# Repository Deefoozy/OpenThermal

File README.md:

# OpenThermal
Thermal camera project

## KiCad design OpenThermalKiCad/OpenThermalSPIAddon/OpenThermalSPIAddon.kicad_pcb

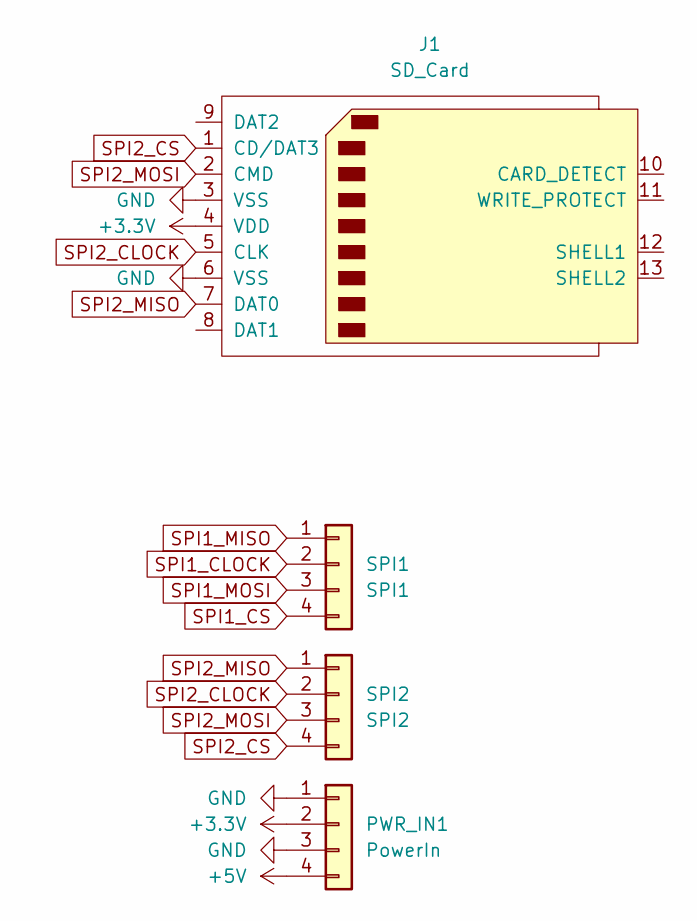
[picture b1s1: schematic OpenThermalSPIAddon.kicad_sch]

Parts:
J1: SD_Card; SD_Kyocera_145638009211859+
PWR_IN1: PowerIn; PinSocket_1x04_P2.54mm_Vertical
SPI1: SPI1; PinSocket_1x04_P2.54mm_Vertical
SPI2: SPI2; PinSocket_1x04_P2.54mm_Vertical

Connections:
+3.3V: J1.4 (VDD), PWR_IN1.2
+5V: PWR_IN1.4
GND: J1.3 (VSS), J1.6 (VSS), PWR_IN1.1, PWR_IN1.3
SPI1_CLOCK: SPI1.2
SPI1_CS: SPI1.4
SPI1_MISO: SPI1.1
SPI1_MOSI: SPI1.3
SPI2_CLOCK: J1.5 (CLK), SPI2.2
SPI2_CS: J1.1 (CD/DAT3), SPI2.4
SPI2_MISO: J1.7 (DAT0), SPI2.1
SPI2_MOSI: J1.2 (CMD), SPI2.3

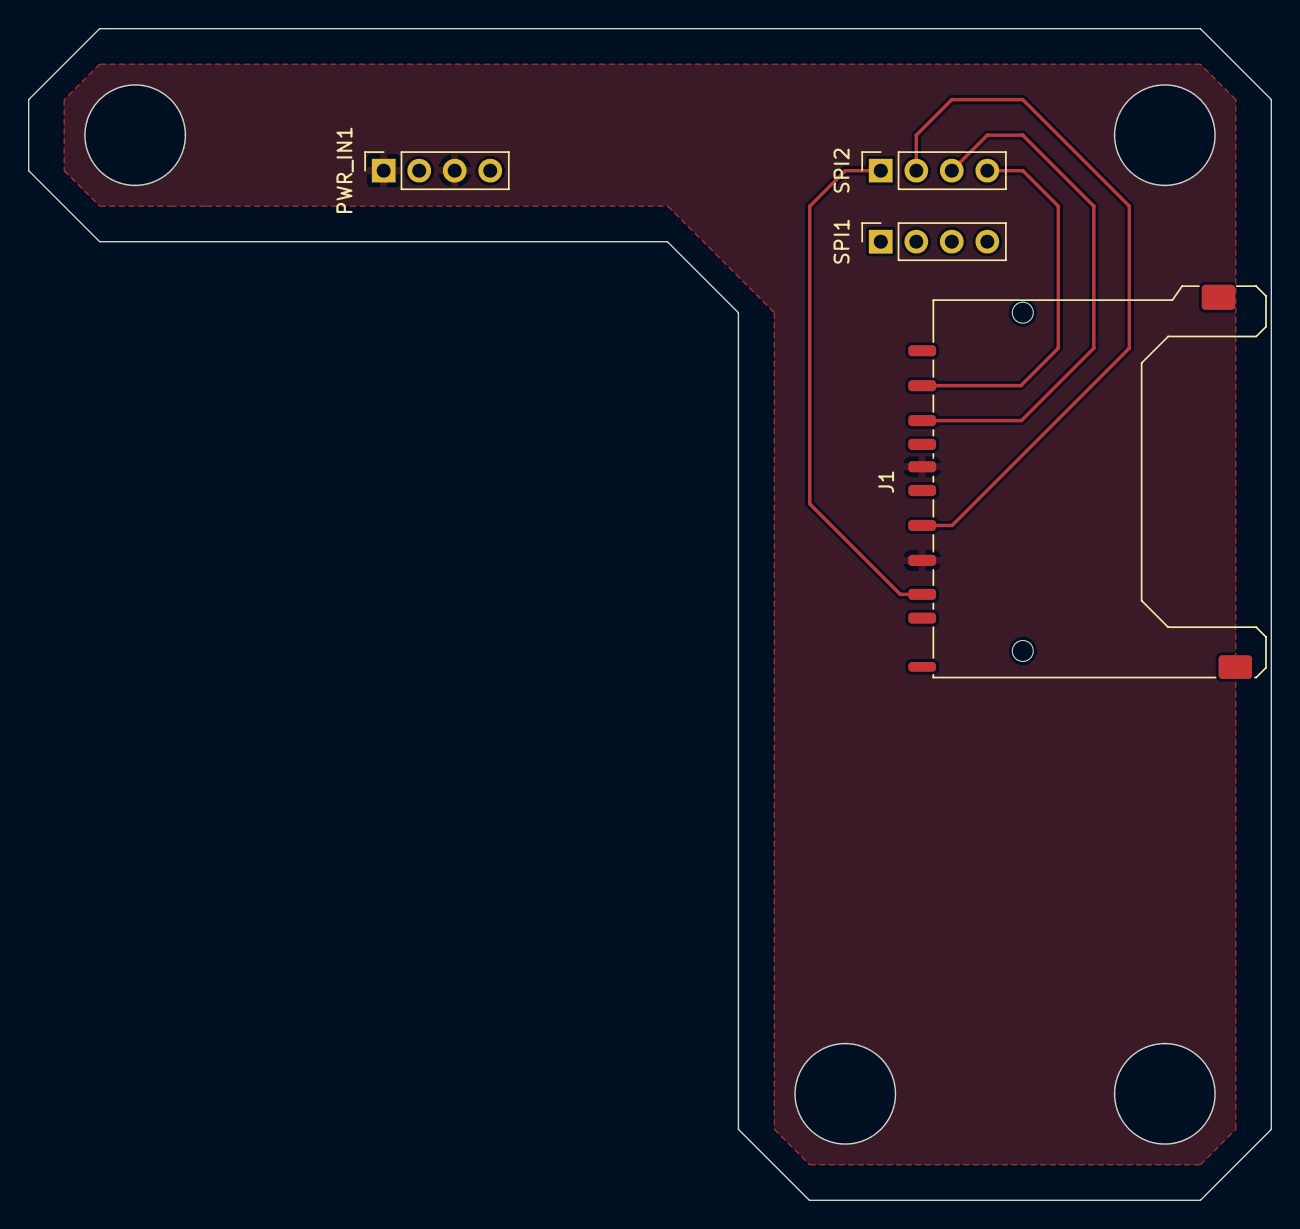
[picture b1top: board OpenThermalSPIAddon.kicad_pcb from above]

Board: 2 copper layers, 88.9 x 83.8 mm, 4 parts (0 on the bottom side), 6 nets.

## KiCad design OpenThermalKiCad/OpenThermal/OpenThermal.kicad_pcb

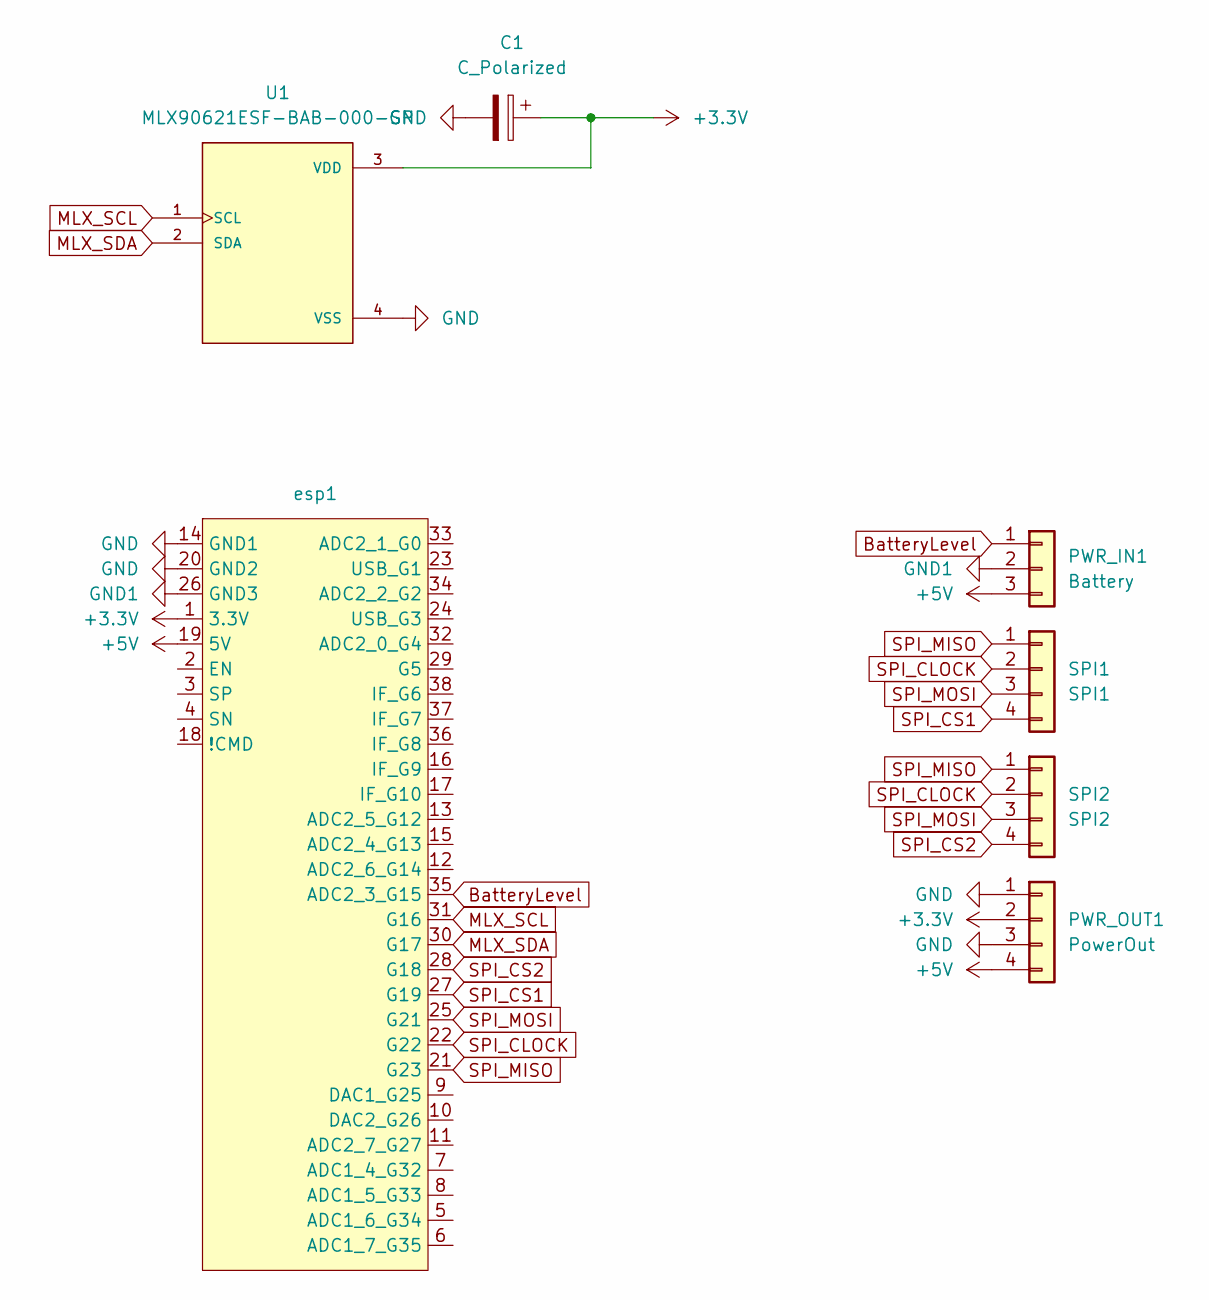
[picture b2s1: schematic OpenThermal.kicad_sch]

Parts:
C1: C_Polarized; C_Disc_D4.3mm_W1.9mm_P5.00mm
PWR_IN1: Battery; PinSocket_1x03_P2.54mm_Vertical
PWR_OUT1: PowerOut; PinSocket_1x04_P2.54mm_Vertical
SPI1: SPI1; PinSocket_1x04_P2.54mm_Vertical
SPI2: SPI2; PinSocket_1x04_P2.54mm_Vertical
U1: MLX90621ESF-BAB-000-SP; TO292P930H600-4
esp1: AZdelivery_nodemcu_esp32

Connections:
+3.3V: C1.1, PWR_OUT1.2, U1.3 (VDD), esp1.1 (3.3V)
+5V: PWR_IN1.3, PWR_OUT1.4, esp1.19 (5V)
BatteryLevel: PWR_IN1.1, esp1.35 (ADC2_3_G15)
GND: C1.2, PWR_OUT1.1, PWR_OUT1.3, U1.4 (VSS), esp1.14 (GND1), esp1.20 (GND2)
GND1: PWR_IN1.2, esp1.26 (GND3)
MLX_SCL: U1.1 (SCL), esp1.31 (G16)
MLX_SDA: U1.2 (SDA), esp1.30 (G17)
SPI_CLOCK: SPI1.2, SPI2.2, esp1.22 (G22)
SPI_CS1: SPI1.4, esp1.27 (G19)
SPI_CS2: SPI2.4, esp1.28 (G18)
SPI_MISO: SPI1.1, SPI2.1, esp1.21 (G23)
SPI_MOSI: SPI1.3, SPI2.3, esp1.25 (G21)

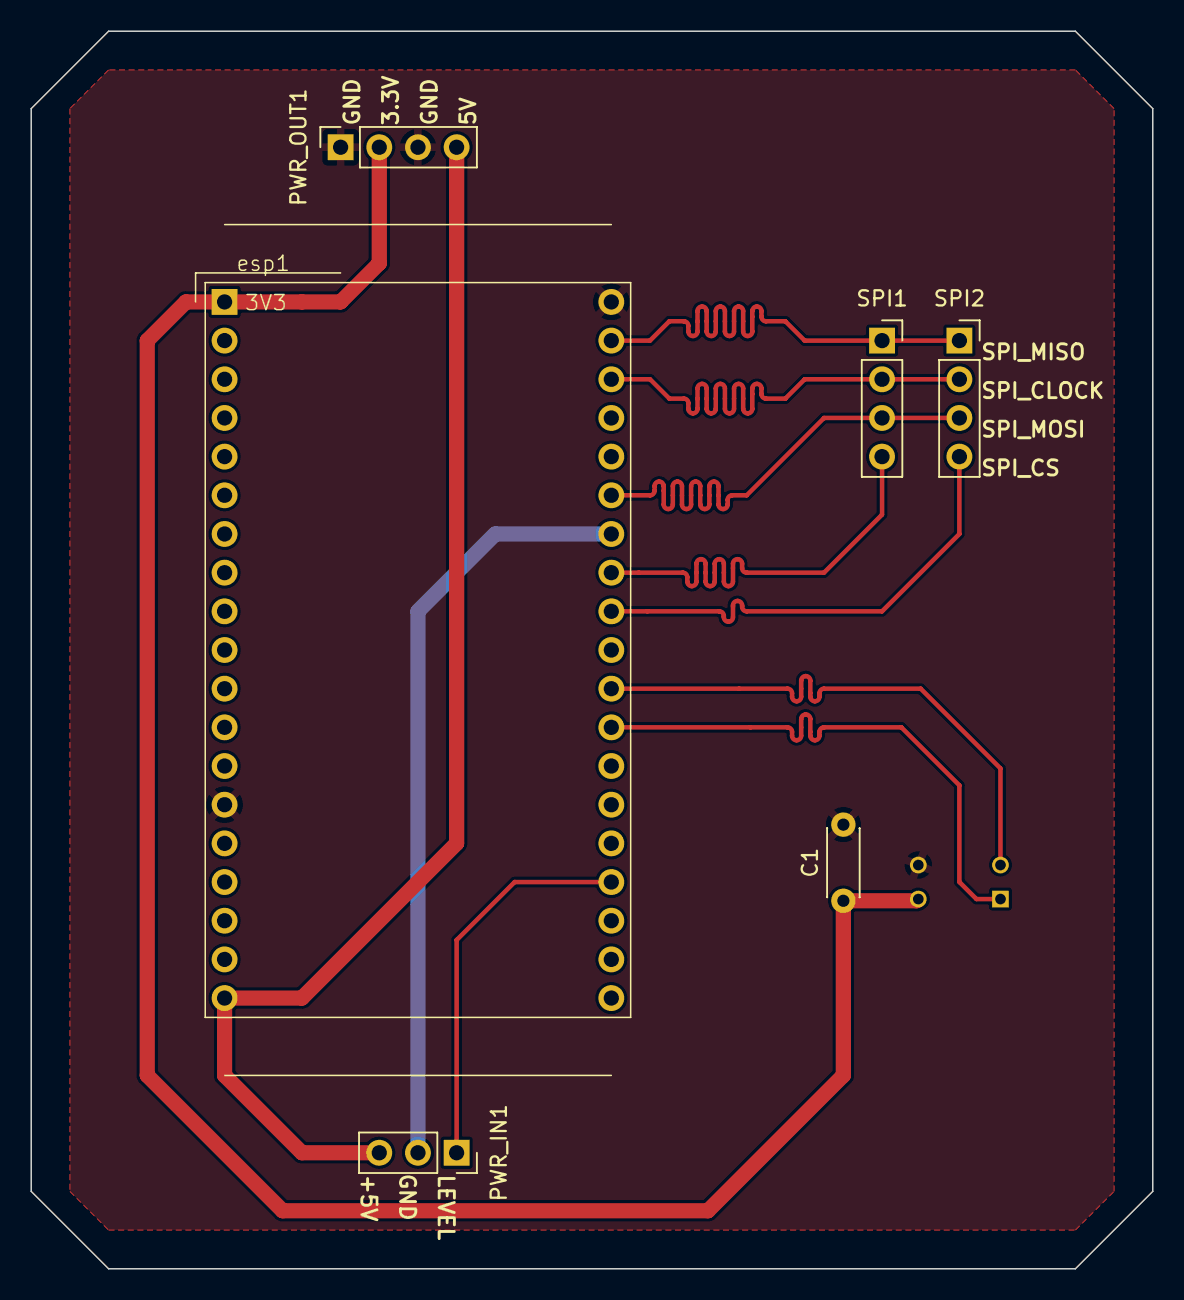
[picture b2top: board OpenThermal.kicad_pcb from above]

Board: 2 copper layers, 73.7 x 81.3 mm, 7 parts (1 on the bottom side), 12 nets.

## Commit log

2023-11-28 added kicad project and gitignore
2023-12-10 Updated gitignore
2023-12-10 Updated project
2024-02-14 Updated camera module
2024-02-15 split project
2024-02-20 Updated wiring and placement
2024-02-20 Updated wiring + components
2024-12-05 Updated main
